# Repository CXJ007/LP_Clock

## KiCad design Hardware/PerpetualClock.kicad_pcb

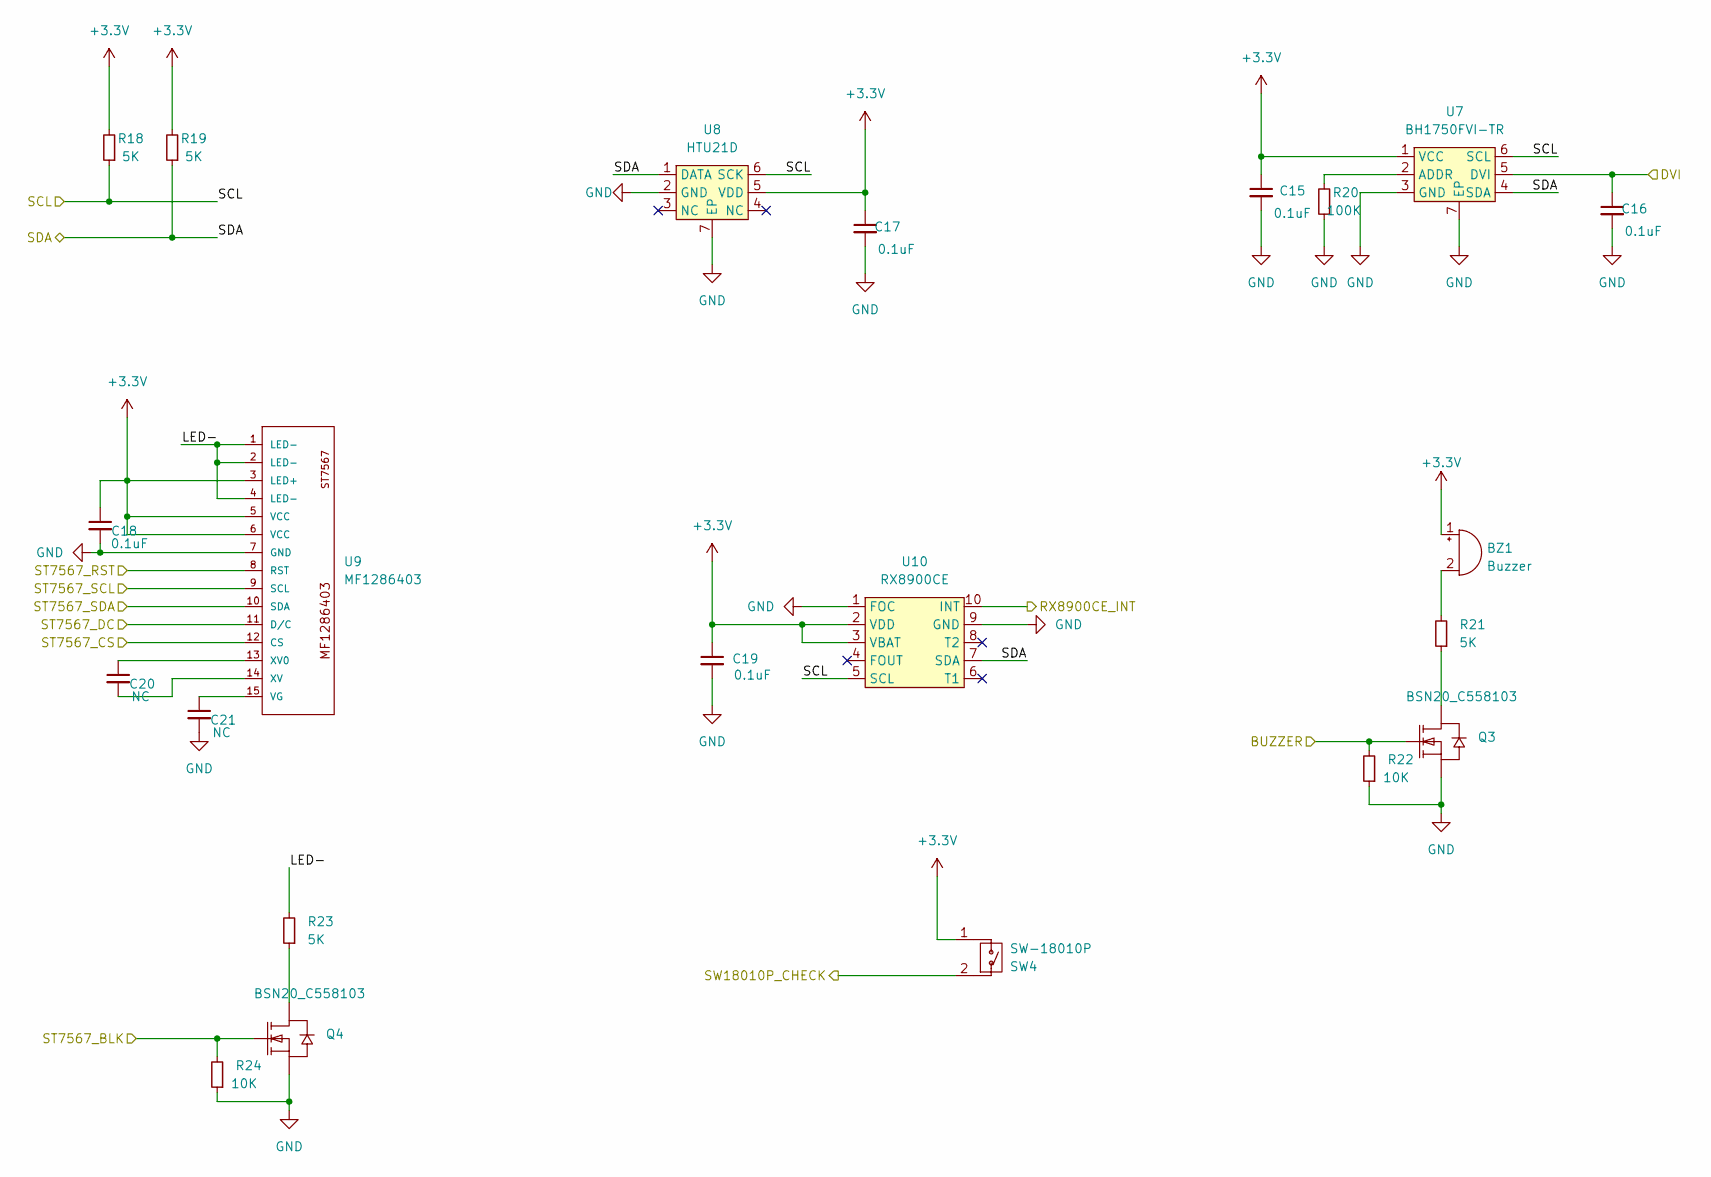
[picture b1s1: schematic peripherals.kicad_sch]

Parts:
BZ1: Buzzer; MagneticBuzzer_PUI_AT-0927-TT-6-R
C15, C16, C17, C18, C19: 0.1uF; C_0603_1608Metric
C20, C21: NC; C_0603_1608Metric
Q3, Q4: BSN20_C558103; SOT-23-3_L2.9-W1.3-P1.90-LS2.4-BR
R18, R19, R21, R23: 5K; R_0603_1608Metric
R20: 100K; R_0603_1608Metric
R22, R24: 10K; R_0603_1608Metric
SW4: SW-18010P; SW-TH_SW-18010P
U7: BH1750FVI-TR; WSOF-6_L2.6-W1.6-P0.50-TL-EP
U8: HTU21D; DFN-6-1EP_3x3mm_P1mm_EP1.5x2.4mm
U9: MF1286403
U10: RX8900CE; EPSON_CE-USON-10_USON-10_3.2x2.5mm_P0.7mm

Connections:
+3.3V: BZ1.1 (-), C15.1, C17.1, C18.1, C19.1, R18.2, R19.2, SW4.1, U7.1 (VCC), U8.5 (VDD), U9.3 (LED+), U9.5 (VCC), U9.6 (VCC), U10.2 (VDD), U10.3 (VBAT); also elsewhere on the board
/MCU/PA2: SW4.2; also elsewhere on the board
/MCU/PA3: Q3.1 (G), R22.2; also elsewhere on the board
/MCU/PA5: Q4.1 (G), R24.2; also elsewhere on the board
/MCU/PA8: C16.1, U7.5 (DVI); also elsewhere on the board
/MCU/PA9: R18.1, U7.6 (SCL), U8.6 (SCK), U10.5 (SCL); also elsewhere on the board
/MCU/PA10: R19.1, U7.4 (SDA), U8.1 (DATA), U10.7 (SDA); also elsewhere on the board
/MCU/PA15: U9.12 (CS); also elsewhere on the board
/MCU/PB1: U10.10 (INT); also elsewhere on the board
/MCU/PB3: U9.9 (SCL); also elsewhere on the board
/MCU/PB5: U9.10 (SDA); also elsewhere on the board
/MCU/PB6: U9.11 (D/C); also elsewhere on the board
/MCU/PB7: U9.8 (RST); also elsewhere on the board
/peripherals/LED-: R23.2, U9.1 (LED-), U9.2 (LED-), U9.4 (LED-)
GND: C15.2, C16.2, C17.2, C18.2, C19.2, C21.2, Q3.2 (S), Q4.2 (S), R20.1, R22.1, R24.1, U7.3 (GND), U7.7 (EP), U8.2 (GND), U8.7 (EP), U9.7 (GND), U10.1 (FOC), U10.9 (GND); also elsewhere on the board
unnamed: BZ1.2 (+), R21.2
unnamed: Q3.3 (D), R21.1
unnamed: Q4.3 (D), R23.1
unnamed: R20.2, U7.2 (ADDR)
unnamed: C21.1, U9.15 (VG)
unnamed: C20.1, U9.13 (XV0)
unnamed: C20.2, U9.14 (XV)

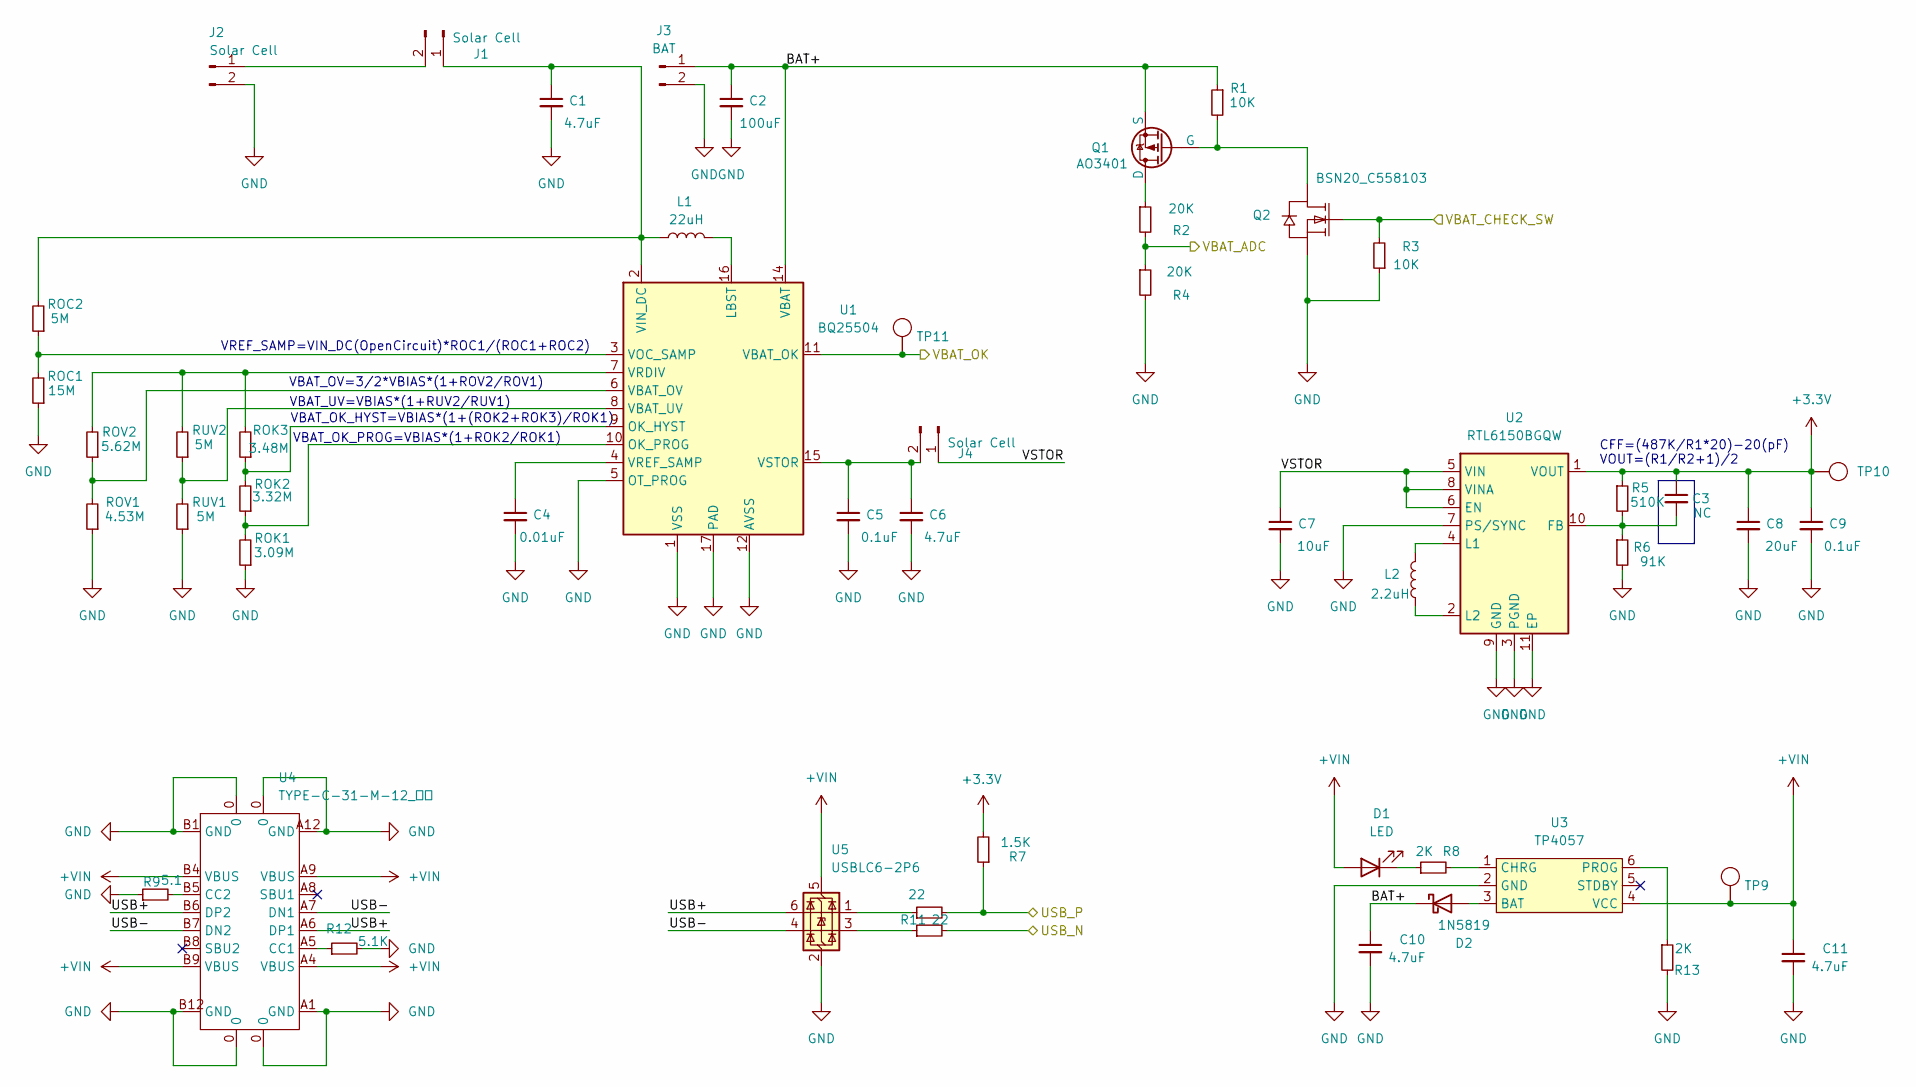
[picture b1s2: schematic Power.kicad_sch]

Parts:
C1, C6, C10, C11: 4.7uF; C_0603_1608Metric
C2: 100uF; C_0603_1608Metric
C3: NC; C_0603_1608Metric
C4: 0.01uF; C_0603_1608Metric
C5, C9: 0.1uF; C_0603_1608Metric
C7: 10uF; C_0603_1608Metric
C8: 20uF; C_0603_1608Metric
D1: LED; LED_0402_1005Metric
D2: 1N5819; D_SMA
J1, J2, J4: Solar Cell; 2p_2.54
J3: BAT; 2p_2.54
L1: 22uH; L_Chilisin_BMRx00060630
L2: 2.2uH; L2.2uh 2A
Q1: AO3401; SOT-23
Q2: BSN20_C558103; SOT-23-3_L2.9-W1.3-P1.90-LS2.4-BR
R1, R3: 10K; R_0603_1608Metric
R2, R4: 20K; R_0603_1608Metric
R5: 510K; R_0603_1608Metric
R6: 91K; R_0603_1608Metric
R7: 1.5K; R_0603_1608Metric
R8, R13: 2K; R_0603_1608Metric
R9: 5.1; R_0603_1608Metric
R10, R11: 22; R_0603_1608Metric
R12: 5.1K; R_0603_1608Metric
ROC1: 15M; R_0603_1608Metric
ROC2: 5M; R_0603_1608Metric
ROK1: 3.09M; R_0603_1608Metric
ROK2: 3.32M; R_0603_1608Metric
ROK3: 3.48M; R_0603_1608Metric
ROV1: 4.53M; R_0603_1608Metric
ROV2: 5.62M; R_0603_1608Metric
RUV1, RUV2: 5M; R_0603_1608Metric
TP9, TP10, TP11: TP
U1: BQ25504; VQFN-16-1EP_3x3mm_P0.5mm_EP1.68x1.68mm
U2: RTL6150BGQW; WSON-10-1EP_2.5x2.5mm_P0.5mm_EP1.2x2mm
U3: TP4057; SOT-23-6
U4: TYPE-C-31-M-12_母座; typec 12
U5: USBLC6-2P6; SOT-666

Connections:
+3.3V: C3.1, C8.1, C9.1, R5.1, R7.2, TP10.1, U2.1 (VOUT); also elsewhere on the board
+VIN: C11.1, D1.2 (A), TP9.1, U3.4 (VCC), U4.A4 (VBUS), U4.A9 (VBUS), U4.B4 (VBUS), U4.B9 (VBUS), U5.5 (VBUS)
/MCU/PA1: R2.2, R4.1; also elsewhere on the board
/MCU/PC14: Q2.1 (G), R3.2; also elsewhere on the board
/MCU/PC15: TP11.1, U1.11 (VBAT_OK); also elsewhere on the board
/MCU/USB_N: R11.2; also elsewhere on the board
/MCU/USB_P: R7.1, R10.2; also elsewhere on the board
/Power/BAT+: C2.1, C10.1, D2.1 (K), J3.1, Q1.2 (S), R1.1, U1.14 (VBAT)
/Power/USB+: U4.A6 (DP1), U4.B6 (DP2), U5.6 (I/O1)
/Power/USB-: U4.A7 (DN1), U4.B7 (DN2), U5.4 (I/O2)
/Power/VSTOR: C7.1, J4.1, U2.5 (VIN), U2.6 (EN), U2.8 (VINA)
GND: C1.2, C2.2, C4.2, C5.2, C6.2, C7.2, C8.2, C9.2, C10.2, C11.2, J2.2, J3.2, Q2.2 (S), R3.1, R4.2, R6.2, R9.1, R12.2, R13.2, ROC1.1, ROK1.1, ROV1.1, RUV1.1, U1.1 (VSS), U1.5 (OT_PROG), U1.12 (AVSS), U1.13 (VSS), U1.17 (PAD), U2.3 (PGND), U2.7 (PS/SYNC), U2.9 (GND), U2.11 (EP), U3.2 (GND), U4.0, U4.A1 (GND), U4.A12 (GND), U4.B1 (GND), U4.B12 (GND), U5.2 (GND); also elsewhere on the board
unnamed: D1.1 (K), R8.1
unnamed: D2.2 (A), U3.3 (BAT)
unnamed: C1.1, J1.1, L1.1, ROC2.2, U1.2 (VIN_DC)
unnamed: J1.2, J2.1
unnamed: C5.1, C6.1, J4.2, U1.15 (VSTOR)
unnamed: Q1.3 (D), R2.1
unnamed: Q1.1 (G), Q2.3 (D), R1.2
unnamed: R10.1, U5.1 (I/O1)
unnamed: R11.1, U5.3 (I/O2)
unnamed: L1.2, U1.16 (LBST)
unnamed: ROK2.2, ROK3.1, U1.9 (OK_HYST)
unnamed: ROK1.2, ROK2.1, U1.10 (OK_PROG)
unnamed: ROV1.2, ROV2.1, U1.6 (VBAT_OV)
unnamed: RUV1.2, RUV2.1, U1.8 (VBAT_UV)
unnamed: ROC1.2, ROC2.1, U1.3 (VOC_SAMP)
unnamed: ROK3.2, ROV2.2, RUV2.2, U1.7 (VRDIV)
unnamed: C4.1, U1.4 (VREF_SAMP)
unnamed: C3.2, R5.2, R6.1, U2.10 (FB)
unnamed: L2.2, U2.4 (L1)
unnamed: L2.1, U2.2 (L2)
unnamed: R8.2, U3.1 (CHRG)
unnamed: R13.1, U3.6 (PROG)
unnamed: R12.1, U4.A5 (CC1)
unnamed: R9.2, U4.B5 (CC2)

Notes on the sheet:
VBAT_OV=3/2*VBIAS*(1+ROV2/ROV1)
VREF_SAMP=VIN_DC(OpenCircuit)*ROC1/(ROC1+ROC2)
VOUT=(R1/R2+1)/2
CFF=(487K/R1*20)-20(pF)
VBAT_OK_HYST=VBIAS*(1+(ROK2+ROK3)/ROK1)
VBAT_UV=VBIAS*(1+RUV2/RUV1)
VBAT_OK_PROG=VBIAS*(1+ROK2/ROK1)

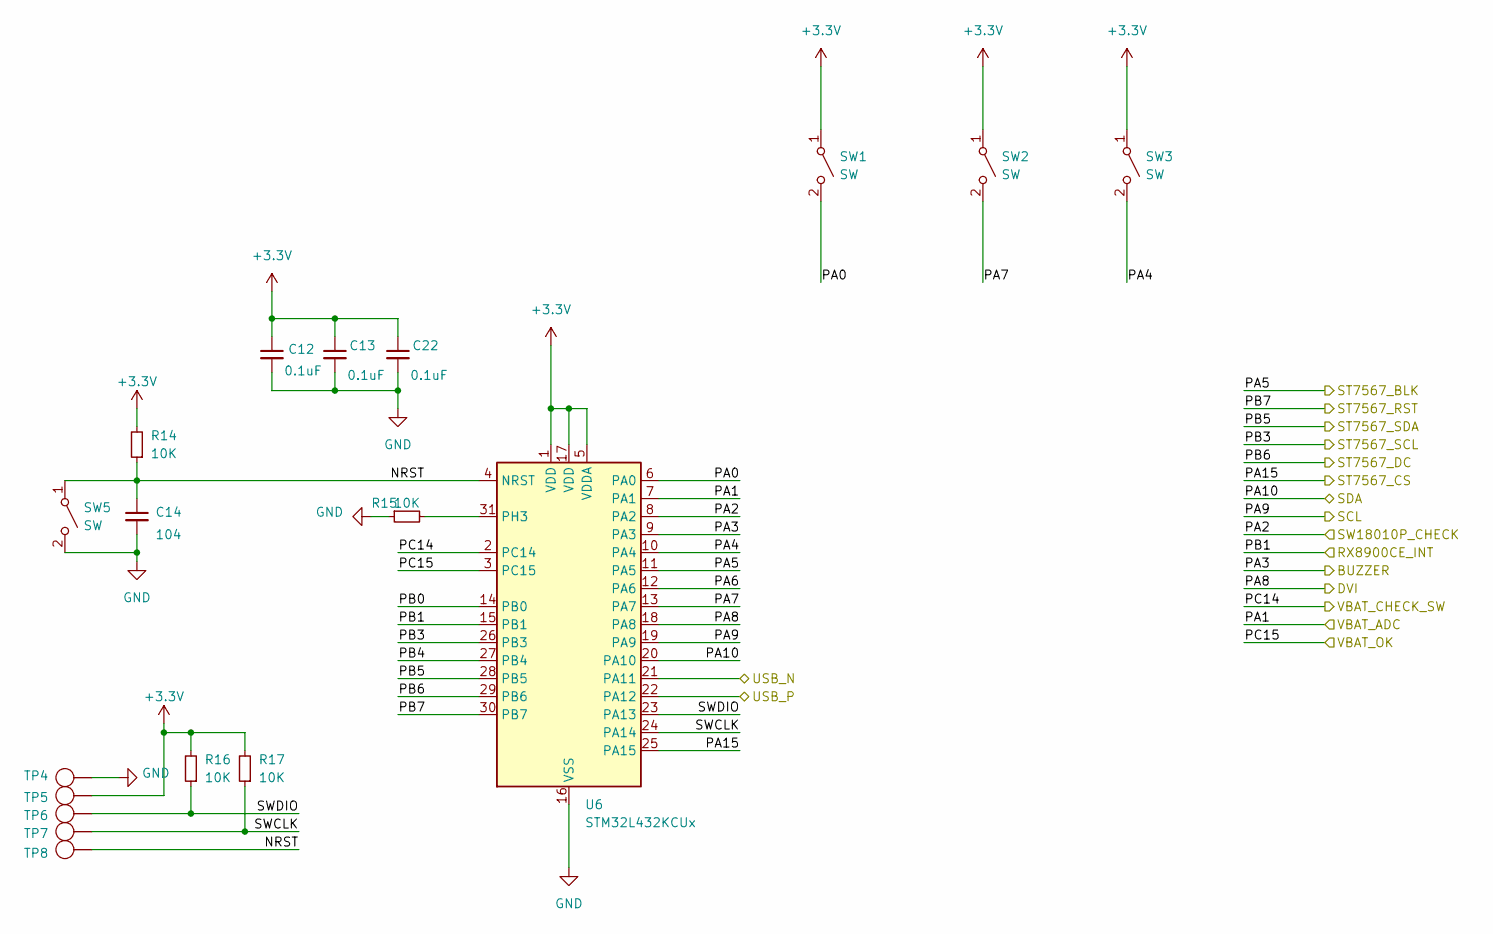
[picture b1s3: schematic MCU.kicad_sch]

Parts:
C12, C13, C22: 0.1uF; C_0603_1608Metric
C14: 104; C_0603_1608Metric
R14, R15, R16, R17: 10K; R_0603_1608Metric
SW1, SW2, SW3: SW; SW-SMD_L4.7-W3.5-P3.35-EH
SW5: SW; SW-SMD_L4.0-W2.9-LS5.0
TP4, TP5, TP6, TP7, TP8: TP
U6: STM32L432KCUx; QFN-32-1EP_5x5mm_P0.5mm_EP3.45x3.45mm

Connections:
+3.3V: C12.1, C13.1, C22.1, R14.2, R16.2, R17.2, SW1.1 (A), SW2.1 (A), SW3.1 (A), TP5.1, U6.1 (VDD), U6.5 (VDDA), U6.17 (VDD); also elsewhere on the board
/MCU/NRST: C14.1, R14.1, SW5.1 (A), TP8.1, U6.4 (NRST)
/MCU/PA0: SW1.2 (B), U6.6 (PA0)
/MCU/PA1: U6.7 (PA1); also elsewhere on the board
/MCU/PA2: U6.8 (PA2); also elsewhere on the board
/MCU/PA3: U6.9 (PA3); also elsewhere on the board
/MCU/PA4: SW3.2 (B), U6.10 (PA4)
/MCU/PA5: U6.11 (PA5); also elsewhere on the board
/MCU/PA6: U6.12 (PA6)
/MCU/PA7: SW2.2 (B), U6.13 (PA7)
/MCU/PA8: U6.18 (PA8); also elsewhere on the board
/MCU/PA9: U6.19 (PA9); also elsewhere on the board
/MCU/PA10: U6.20 (PA10); also elsewhere on the board
/MCU/PA15: U6.25 (PA15); also elsewhere on the board
/MCU/PB0: U6.14 (PB0)
/MCU/PB1: U6.15 (PB1); also elsewhere on the board
/MCU/PB3: U6.26 (PB3); also elsewhere on the board
/MCU/PB4: U6.27 (PB4)
/MCU/PB5: U6.28 (PB5); also elsewhere on the board
/MCU/PB6: U6.29 (PB6); also elsewhere on the board
/MCU/PB7: U6.30 (PB7); also elsewhere on the board
/MCU/PC14: U6.2 (PC14); also elsewhere on the board
/MCU/PC15: U6.3 (PC15); also elsewhere on the board
/MCU/SWCLK: R17.1, TP7.1, U6.24 (PA14)
/MCU/SWDIO: R16.1, TP6.1, U6.23 (PA13)
/MCU/USB_N: U6.21 (PA11); also elsewhere on the board
/MCU/USB_P: U6.22 (PA12); also elsewhere on the board
GND: C12.2, C13.2, C14.2, C22.2, R15.1, SW1.3, SW1.4, SW2.3, SW2.4, SW3.3, SW3.4, SW5.2 (B), TP4.1, U6.16 (VSS), U6.32 (VSS), U6.33 (VSS); also elsewhere on the board
unnamed: R15.2, U6.31 (PH3)

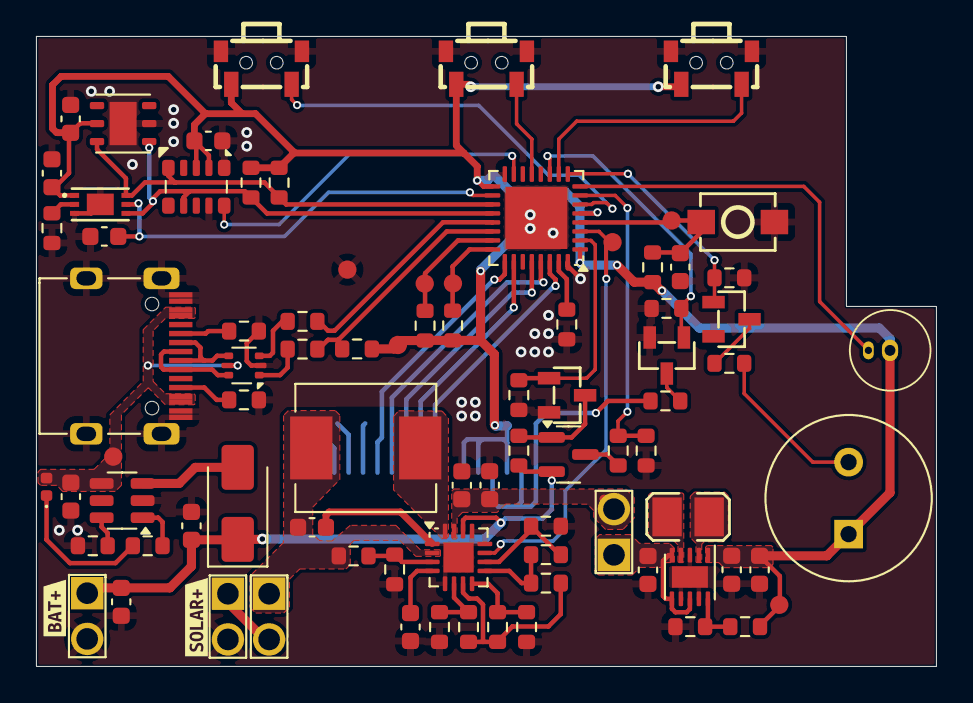
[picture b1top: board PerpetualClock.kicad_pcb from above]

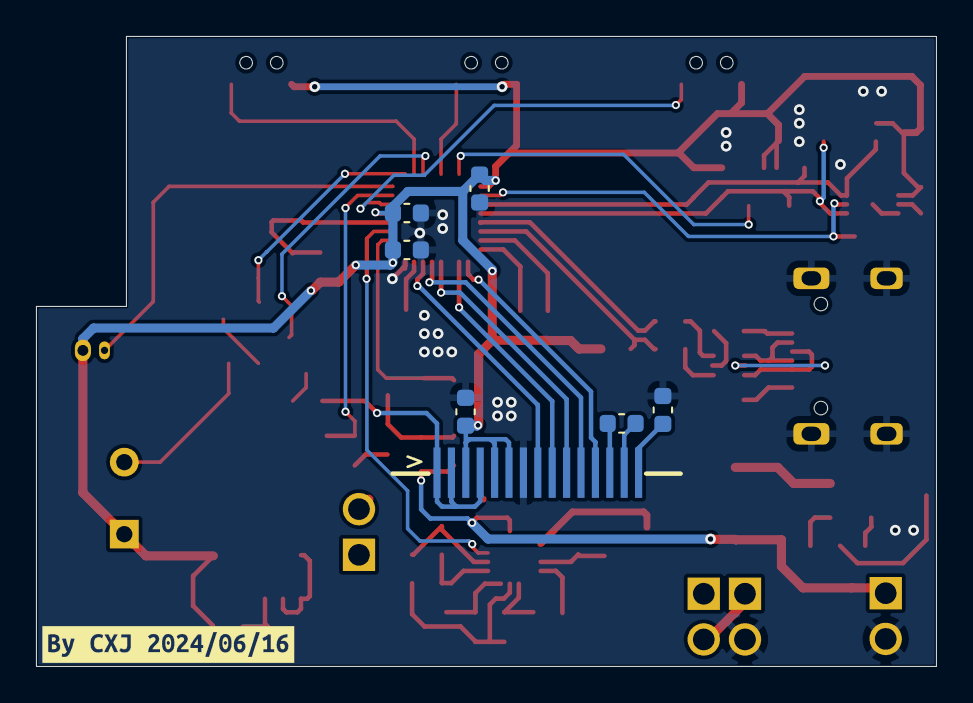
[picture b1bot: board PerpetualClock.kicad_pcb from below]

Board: 2 copper layers, 50.0 x 35.0 mm, 93 parts (8 on the bottom side), 63 nets.

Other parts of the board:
kibuzzard-666E94AD: G***; kibuzzard-666E94AD
kibuzzard-666E9537: G***; kibuzzard-666E9537
kibuzzard-666E9566: G***; kibuzzard-666E9566

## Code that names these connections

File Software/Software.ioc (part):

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Mcu.Name=STM32L432K(B-C)Ux
Mcu.Package=UFQFPN32
Mcu.UserName=STM32L432KCUx
PA0.GPIOParameters=GPIO_PuPd
PA0.GPIO_PuPd=GPIO_PULLDOWN
PA0.Signal=GPIO_Input
PA10.Mode=I2C
PA10.Signal=I2C1_SDA
PA13\ (JTMS-SWDIO).Mode=Serial_Wire
PA13\ (JTMS-SWDIO).Signal=SYS_JTMS-SWDIO
PA14\ (JTCK-SWCLK).Mode=Serial_Wire
PA14\ (JTCK-SWCLK).Signal=SYS_JTCK-SWCLK
PA3.Signal=GPIO_Output
PA4.GPIOParameters=GPIO_PuPd
PA4.GPIO_PuPd=GPIO_PULLDOWN
PA4.Signal=GPIO_Input
PA7.GPIOParameters=GPIO_PuPd
PA7.GPIO_PuPd=GPIO_PULLDOWN
PA7.Signal=GPIO_Input
PA8.Signal=GPIO_Output
PA9.Mode=I2C
PA9.Signal=I2C1_SCL
PB1.GPIOParameters=GPIO_PuPd,GPIO_ModeDefaultEXTI
PB1.GPIO_ModeDefaultEXTI=GPIO_MODE_IT_FALLING
PB1.GPIO_PuPd=GPIO_PULLUP
PB1.Signal=GPXTI1
RCC.HSE_VALUE=8000000
RCC.SYSCLKFreq_VALUE=80000000
RCC.SYSCLKSource=RCC_SYSCLKSOURCE_PLLCLK
board=custom

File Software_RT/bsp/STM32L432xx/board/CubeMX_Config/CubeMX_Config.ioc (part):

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Mcu.Name=STM32L432K(B-C)Ux
Mcu.Package=UFQFPN32
Mcu.UserName=STM32L432KCUx
PA10.GPIOParameters=GPIO_PuPd,GPIO_ModeDefaultOutputPP
PA10.GPIO_ModeDefaultOutputPP=GPIO_MODE_OUTPUT_OD
PA10.GPIO_PuPd=GPIO_NOPULL
PA10.Signal=GPIO_Output
PA11.Mode=Device
PA11.Signal=USB_DM
PA12.Mode=Device
PA12.Signal=USB_DP
PA13\ (JTMS-SWDIO).Mode=Serial_Wire
PA13\ (JTMS-SWDIO).Signal=SYS_JTMS-SWDIO
PA14\ (JTCK-SWCLK).Mode=Serial_Wire
PA14\ (JTCK-SWCLK).Signal=SYS_JTCK-SWCLK
PA9.GPIOParameters=GPIO_PuPd,GPIO_ModeDefaultOutputPP
PA9.GPIO_ModeDefaultOutputPP=GPIO_MODE_OUTPUT_OD
PA9.GPIO_PuPd=GPIO_NOPULL
PA9.Signal=GPIO_Output
PB6.Mode=Asynchronous
PB6.Signal=USART1_TX
PB7.Mode=Asynchronous
PB7.Signal=USART1_RX
RCC.HSE_VALUE=8000000
RCC.SYSCLKFreq_VALUE=80000000
RCC.SYSCLKSource=RCC_SYSCLKSOURCE_PLLCLK
board=custom

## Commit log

2024-06-20 add threadx lower power
2024-06-20 add hardware
2024-06-23 Add RX8900 IIC read write
2024-06-23 Add RX8900 DebugMode
2024-06-28 Add RX8900 set and update time api
2024-06-29 add RX8900 ISR
2024-06-29 Add RX8900 alarm function
2024-07-12 添加lowpowermgr 修复lowpowersleep，偶发唤醒跑飞（频率没有降低到2mhz就进行休眠）
2024-07-14 完善add lptim low power sleep
2024-07-17 添加RTC 1s唤醒一次
2024-07-20 add AppModeCtrl appobj htu21d
2024-07-21 添加HTU21D 功耗1.1ms
2024-07-22 添加 HTU21DCRC8 BH1750FVI
2024-07-27 添加 buzzer
2024-07-28 完成 buzzer的功能
2024-08-04 完成 BH1750FVI添加 规范编码格式 1.26ma
2024-08-25 准备把threadx换成rtthread
2024-09-06 bh1750fvi适配
2024-09-06 添加bh1750fvi
2024-09-08 添加cherry usb cdc acm
2024-09-08 添加工程文件
2024-09-08 调整文件结构
2024-09-18 vcom shell初步适配
2024-09-21 移除usart，完善vcom，添加软件rtc，添加cpuusage
2024-09-30 添加rx8900适配 rtc和alarm
